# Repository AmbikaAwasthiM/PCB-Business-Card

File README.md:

# PCB-Business-Card
Created under the YSWS Outpost

The card is designed to have a LED light up when a phone is brought close to the antennna/NFC chip

The antenna coil sits on the front of the business card, on the border. I removed the F.Mask in these areas to expose the copper, and JCL PCB automatically puts a tin finish over exposed copper, so those areas will come out silver in the final physical product

Final design, as generated by JCLPCB in the order window

# BOM
| # | Item | Amount | Link | Cost |
|---|------|--------|------|-------------|
| 1 | NFC Chip | 1 | [Digikey]([https://www.aliexpress.us/item/3256803521775546.html?spm=a2g0o.productlist.main.22.6478lNgJlNgJEx&algo_pvid=eb010e16-b8d5-433e-b930-93ddb07e16ff&algo_exp_id=eb010e16-b8d5-433e-b930-93ddb07e16ff-21&pdp_ext_f=%7B%22order%22%3A%22178%22%2C%22eval%22%3A%221%22%7D&pdp_npi=4%40dis%21USD%216.18%210.99%21%21%2144.08%217.04%21%402103245417538992995887740e4f41%2112000034536362461%21sea%21US%210%21ABX&curPageLogUid=blshBSuqtFpH&utparam-url=scene%3Asearch%7Cquery_from%3A](https://www.digikey.com/en/products/detail/stmicroelectronics/ST25DV64KC-JF6D3/16359669?gclsrc=aw.ds&gad_source=1&gad_campaignid=17922795960&gbraid=0AAAAADrbLljit8M-cmttiiMXfEQ-k5L0t&gclid=Cj0KCQjwrs7RBhDuARIsAIVfBD2K4eA4M6wnh_kFV4ttFB4Qb6ZAq-KoKYcyp1ffjeM-BJqPADlIJxoaAlK1EALw_wcB)) | 1.80 USD
| 2 | 220nf Capacitor | 5 | [Digikey](https://www.digikey.com/en/products/detail/tdk-corporation/C1608X7S2A104K080AB/2116317?gclsrc=aw.ds&gad_source=1&gad_campaignid=120509955&gbraid=0AAAAADrbLljdOEX9bL1ai4qc400Fe8tzP&gclid=CjwKCAjw6f3RBhApEiwAMaCqWUcl6Q0ifo7pvMXdo7gAZ45IDD4X4jxvLfIIFltJTsaX5AIY6ZwZDRoC7dUQAvD_BwE) | .75 USD |
| 3 | LED | 5 | [Digikey]([https://www.amazon.com/GLORIOUS-Gateron-Mechanical-Keyboard-Switches/dp/B07CVQ7ZRL/ref=sr_1_4_sspa?crid=10XHCKI24AHF1&keywords=clear%2Bred%2Bcherry%2Bmx%2Bswitches%2B100pc&qid=1753900124&sprefix=clear%2Bred%2Bcherry%2Bmx%2Bswitches%2B100pc%2Caps%2C106&sr=8-4-spons&sp_csd=d2lkZ2V0TmFtZT1zcF9tdGY&th=1](https://www.digikey.com/en/products/detail/w%C3%BCrth-elektronik/150080SS75000/4489921)) | .95 USD |
| 4 | 47 ohm Resistor | 5 | [Digikey]([https://www.aliexpress.us/item/3256807457768762.html?spm=a2g0o.productlist.main.3.417bjQLojQLoFM&algo_pvid=5f74a285-dd91-4134-b04f-86eff7bfe1f1&algo_exp_id=5f74a285-dd91-4134-b04f-86eff7bfe1f1-2&pdp_ext_f=%7B%22order%22%3A%22509%22%2C%22eval%22%3A%221%22%7D&pdp_npi=4%40dis%21USD%212.12%210.99%21%21%212.12%210.99%21%402103273e17539009433327470eab0f%2112000041630839428%21sea%21US%210%21ABX&curPageLogUid=wlRKuFiINxac&utparam-url=scene%3Asearch%7Cquery_from%3A](https://www.digikey.com/en/products/detail/panasonic-industry/ERJ-3GEYJ470V/135632)) | .50 USD |
| 5 | PCB | 5 | JCLPCB | 5.12 USD |
|Total price: (including tax)| 28.46  USD | Total price (with shipping): | 24.75 | 

Because the total price is 3 dollars over the limit for the B tier budget, the requested amount is 25 USD.

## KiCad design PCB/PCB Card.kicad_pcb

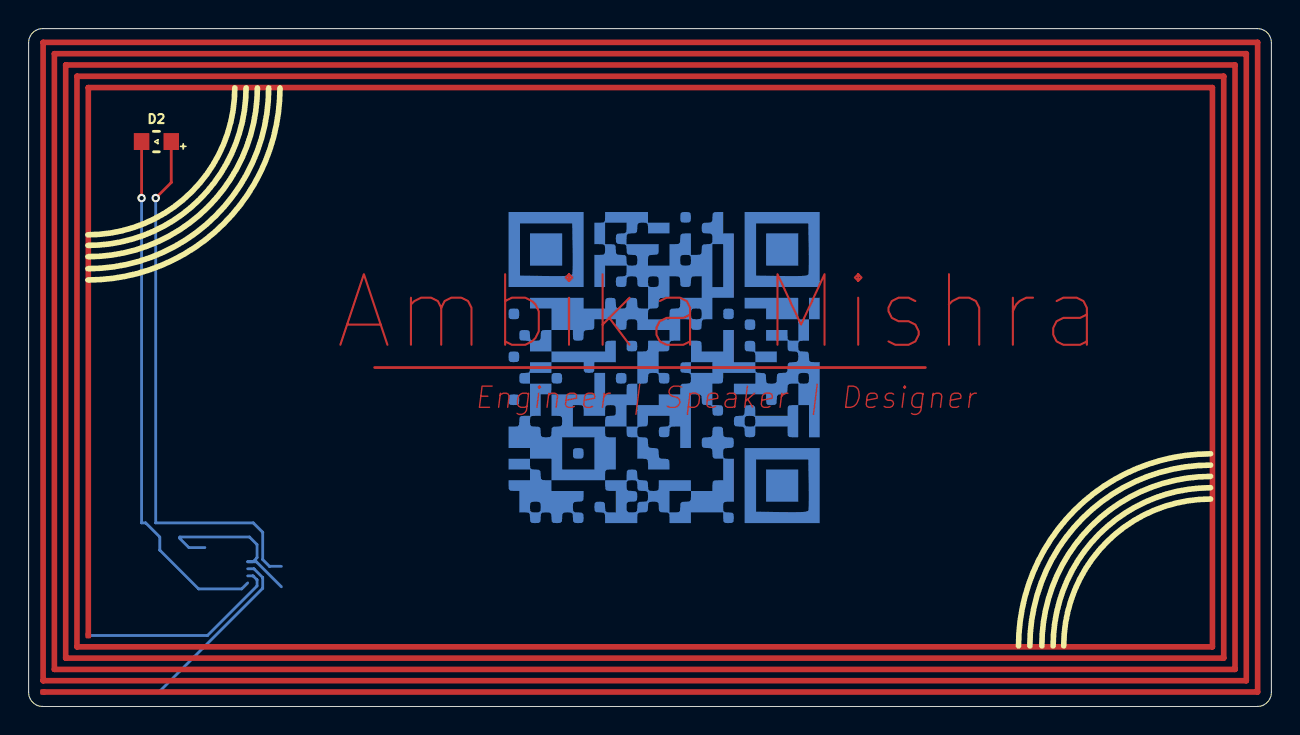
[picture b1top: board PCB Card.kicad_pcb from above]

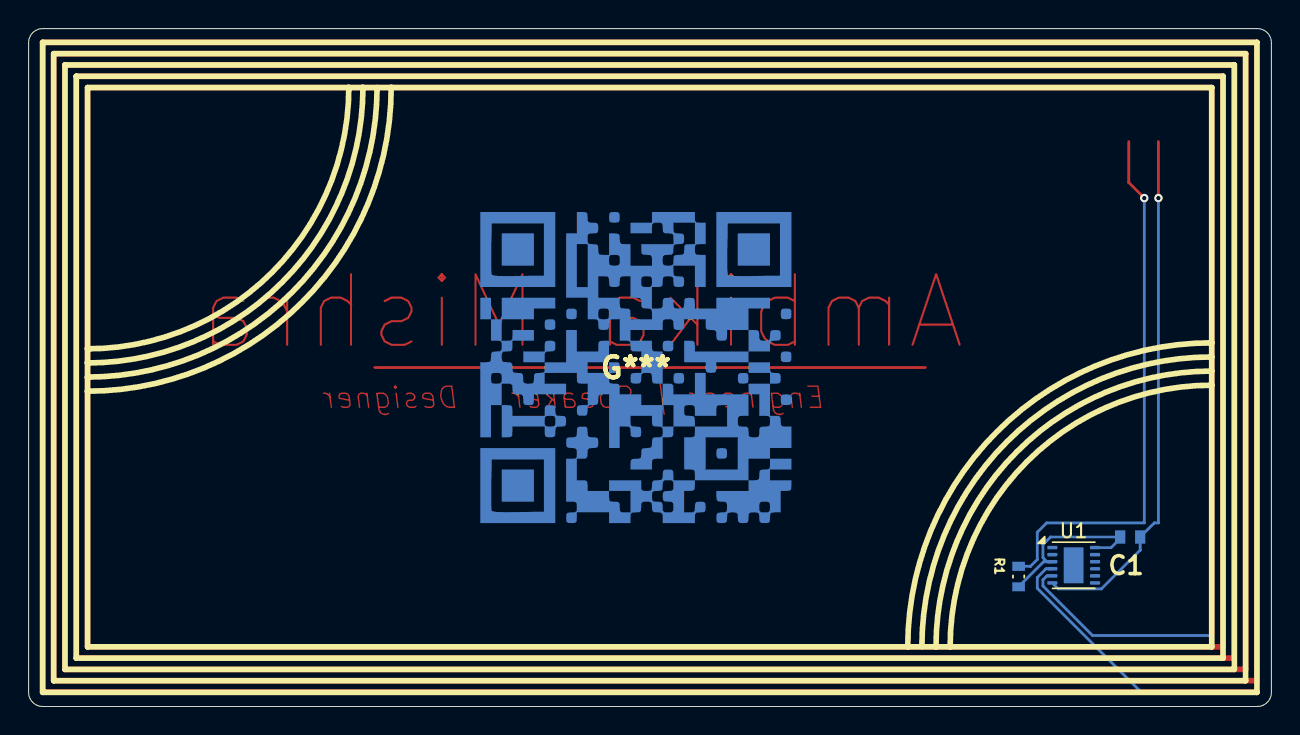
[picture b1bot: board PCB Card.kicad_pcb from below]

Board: 2 copper layers, 88.0 x 48.0 mm, 6 parts (3 on the bottom side), 5 nets.

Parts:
AE1, AE1#2: Antenna_Loop; antennapcbfootprint
C1: C; CAPC1608X90N
D2: LED; WL-SMCW_0805
R1: R; RES_ERJ3GEYJ470V
U1: ST25DV04K-JFR6D3; ST_UFDFPN-12-1EP_3x3mm_P0.5mm_EP1.4x2.55mm

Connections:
unnamed: D2.2 (A), R1.2
unnamed: C1.2, D2.1 (K), U1.6 (VSS)
unnamed: C1.1, R1.1, U1.3 (V_EH), U1.12 (VCC)
coil1: AE1#2.1, U1.4 (AC0)
coil2: AE1#2.2, U1.5 (AC1)

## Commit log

2026-06-27 Add initial README for PCB-Business-Card project
2026-06-27 Create delete
2026-06-28 Create a
2026-06-28 Add BOM.csv with components and pricing details
2026-06-28 Convert BOM.csv to CSV format and update links
    Updated BOM.csv to use comma-separated values format and fixed links.
2026-06-28 Fix formatting and update links in BOM.csv
    Updated BOM.csv to correct formatting and links.
2026-06-28 Update BOM.csv with new component details
2026-06-28 Refactor BOM.csv for improved readability
    Updated BOM.csv format to a more structured layout with separate columns for Link Text and URL.
2026-06-28 Revise README with project info and BOM updates
    Updated the README with project details, BOM, and pricing adjustments.
2026-06-28 Update images in README.md
    Added a new image to the README and removed an old one.
2026-06-28 Modify BOM.csv for NFC Chip quantity and cost
    Updated quantity and total cost for NFC Chip.
2026-06-28 Update BOM.csv with total cost calculations
